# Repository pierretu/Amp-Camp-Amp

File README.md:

# Amp Camp Amp
 Single Ended Class A Amplifier

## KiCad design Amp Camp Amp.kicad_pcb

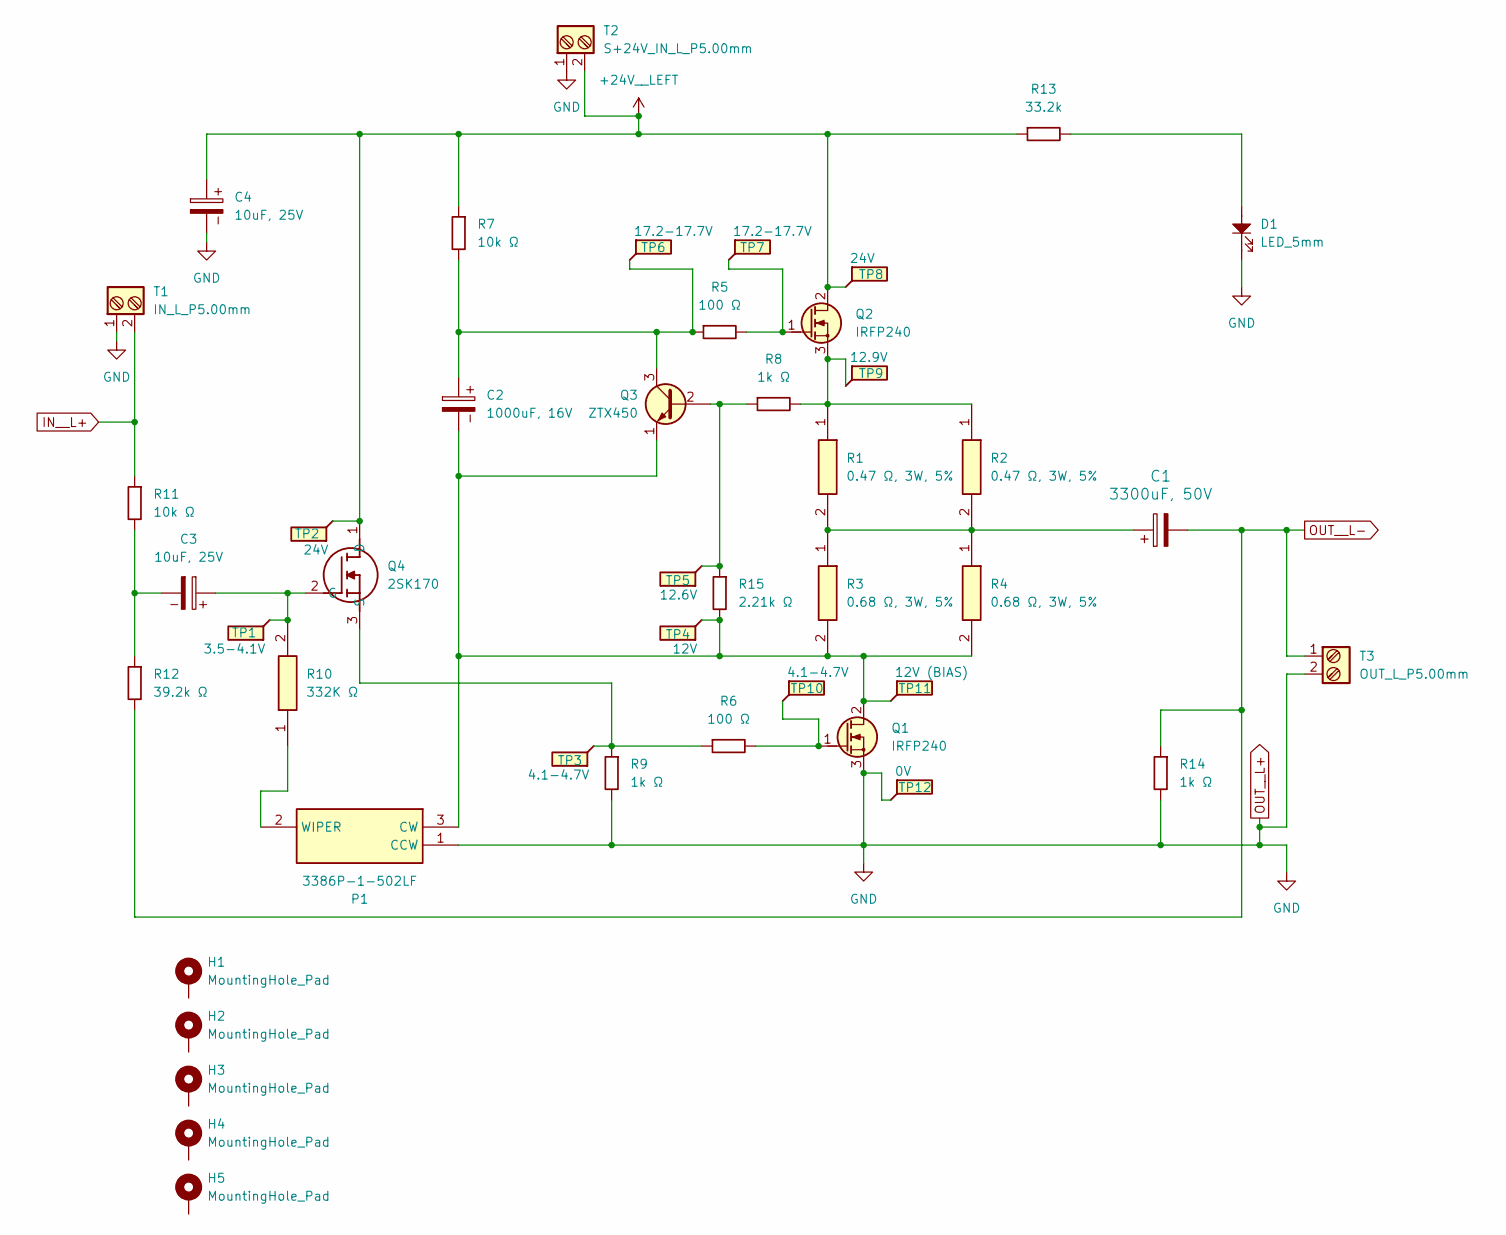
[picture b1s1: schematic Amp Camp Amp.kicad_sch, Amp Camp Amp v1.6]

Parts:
C1: 3300uF, 50V; CP_Radial_D18.0mm_P7.50mm
C2: 1000uF, 16V; CP_Radial_D10.0mm_P5.00mm
C3, C4: 10uF, 25V; CP_Radial_D5.0mm_P2.00mm
D1: LED_5mm; LED_D5.0mm
H1, H2, H3, H4, H5: MountingHole_Pad; MountingHole_2.7mm_Pad
P1: 3386P-1-502LF; 3386P_1; Manufacturer_Part_Number 3386P-1-502LF
Q1, Q2: IRFP240; TO-247-3_Vertical_GDS
Q3: ZTX450; TO-92_Inline_Wide_EBC
Q4: 2SK170; Manufacturer_Part_Number 2SK170
R1, R2: 0.47 Ω, 3W, 5%; RESAD3700W85L1500D550; Manufacturer_Part_Number ERX-3SJR47V
R3, R4: 0.68 Ω, 3W, 5%; RESAD3700W85L1500D550; Manufacturer_Part_Number ERX-3SJR68A
R5, R6: 100 Ω; R_Axial_DIN0207_L6.3mm_D2.5mm_P10.16mm_Horizontal
R7, R11: 10k Ω; R_Axial_DIN0207_L6.3mm_D2.5mm_P10.16mm_Horizontal
R8, R9, R14: 1k Ω; R_Axial_DIN0207_L6.3mm_D2.5mm_P10.16mm_Horizontal
R10: 332K Ω; RESAD1575W64L635D235; Manufacturer_Part_Number RNF14FTD332K
R12: 39.2k Ω; R_Axial_DIN0207_L6.3mm_D2.5mm_P10.16mm_Horizontal
R13: 33.2k; R_Axial_DIN0207_L6.3mm_D2.5mm_P10.16mm_Horizontal
R15: 2.21k Ω; R_Axial_DIN0207_L6.3mm_D2.5mm_P10.16mm_Horizontal
T1: IN_L_P5.00mm; TerminalBlock_Phoenix_PT-1,5-2-5.0-H_1x02_P5.00mm_Horizontal
T2: S+24V_IN_L_P5.00mm; TerminalBlock_Phoenix_PT-1,5-2-5.0-H_1x02_P5.00mm_Horizontal
T3: OUT_L_P5.00mm; TerminalBlock_Phoenix_PT-1,5-2-5.0-H_1x02_P5.00mm_Horizontal
TP1: 3.5-4.1V; TestPoint_Pad_D1.5mm
TP2, TP8: 24V; TestPoint_Pad_D1.5mm
TP3, TP10: 4.1-4.7V; TestPoint_Pad_D1.5mm
TP4: 12V; TestPoint_Pad_D1.5mm
TP5: 12.6V; TestPoint_Pad_D1.5mm
TP6, TP7: 17.2-17.7V; TestPoint_Pad_D1.5mm
TP9: 12.9V; TestPoint_Pad_D1.5mm
TP11: 12V (BIAS); TestPoint_Pad_D1.5mm
TP12: 0V; TestPoint_Pad_D1.5mm

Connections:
+24V__LEFT: C4.1, Q2.2 (D), Q4.1 (D), R7.1, R13.1, T2.2, TP2.1, TP8.1
IN__L+: R11.1, T1.2
unnamed: C1.1, R1.2, R2.2, R3.1, R4.1
unnamed: C3.2, R11.2, R12.1
unnamed: D1.2, R13.2
unnamed: C2.2, P1.3 (CW), Q1.2 (D), Q3.1 (E), R3.2, R4.2, R15.2, TP4.1, TP11.1
unnamed: P1.2 (WIPER), R10.1
unnamed: Q1.1 (G), R6.2, TP10.1
unnamed: Q2.1 (G), R5.2, TP7.1
unnamed: Q2.3 (S), R1.1, R2.1, R8.2, TP9.1
unnamed: Q3.2 (B), R8.1, R15.1, TP5.1
unnamed: C2.1, Q3.3 (C), R5.1, R7.2, TP6.1
unnamed: C3.1, Q4.2 (G), R10.2, TP1.1
unnamed: Q4.3 (S), R6.1, R9.1, TP3.1
OUT__L+: C4.2, D1.1, P1.1 (CCW), Q1.3 (S), R9.2, R14.2, T1.1, T2.1, T3.2, TP12.1
OUT__L-: C1.2, R12.2, R14.1, T3.1

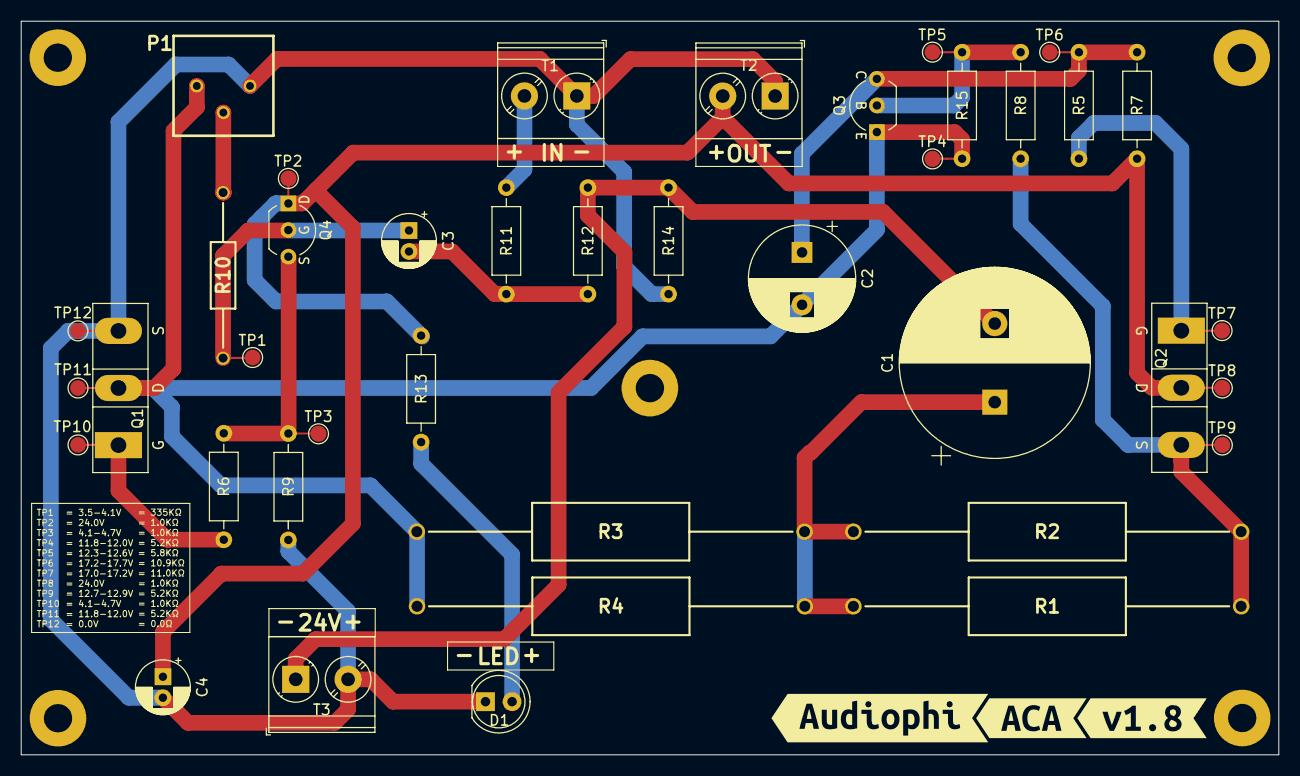
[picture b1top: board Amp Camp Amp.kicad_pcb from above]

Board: 2 copper layers, 120.0 x 70.0 mm, 48 parts (1 on the bottom side), 16 nets.

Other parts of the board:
kibuzzard-673FAD82: G***; kibuzzard-673FAD82
kibuzzard-674CED68: G***; kibuzzard-674CED68
kibuzzard-674D924F: G***; kibuzzard-674D924F

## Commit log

2024-12-02 Updated the board to version 1.8
    List of all differences between V1.6 and V1.8:
    Rear switch is a 3 position DPDT instead of 2 position, necessitating a change in wiring
    Rear panel is printed with a connection diagram
    Chassis rails are improved using weld nuts and secured by bolts
    Blade terminals are included for the front power switch
    Longer wire
2024-12-02 Version change
2024-12-02 Added build guides
2024-12-05 Removed unused files
